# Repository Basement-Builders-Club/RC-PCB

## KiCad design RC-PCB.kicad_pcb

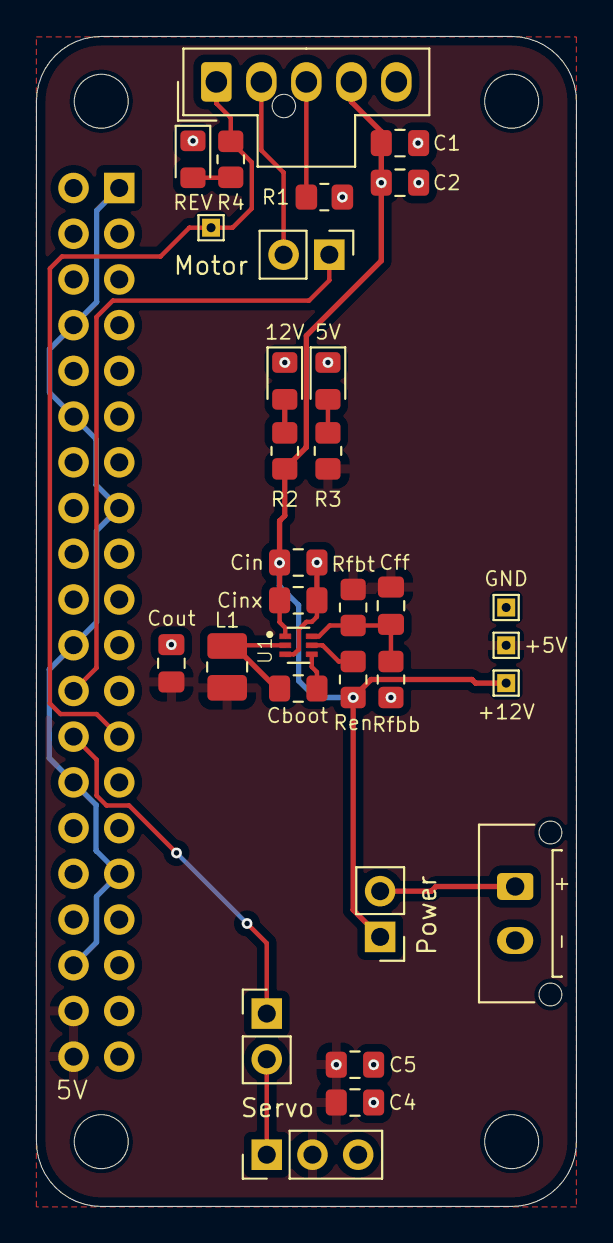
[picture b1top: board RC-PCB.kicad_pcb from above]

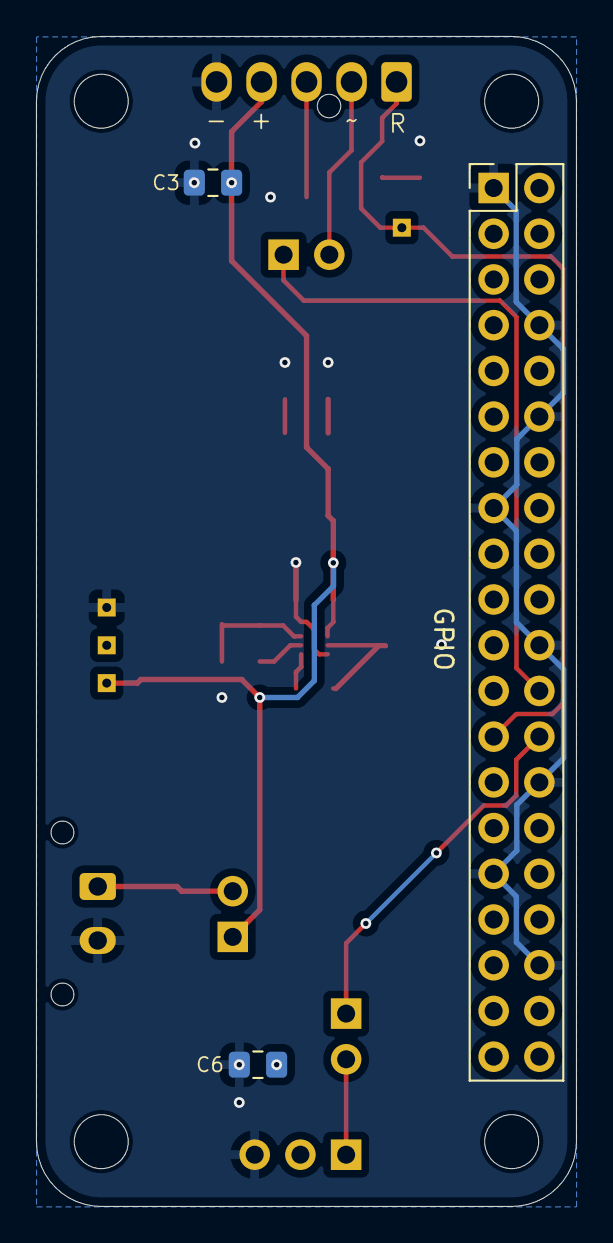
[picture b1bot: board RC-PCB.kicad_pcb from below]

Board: 2 copper layers, 30.0 x 65.0 mm, 38 parts (3 on the bottom side), 17 nets.

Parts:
5V, 12V: LED; LED_0805_2012Metric_Pad1.15x1.40mm_HandSolder
+5V, +12V: TP; TestPoint_THTPad_1.0x1.0mm_Drill0.5mm
Battery1: Conn_01x02; Molex_Micro-Fit_3.0_43650-0215_1x02_P3.00mm_Vertical
C1, C4: .1uF; C_0805_2012Metric_Pad1.18x1.45mm_HandSolder
C2, C3, C5, C6: 10uF; C_0805_2012Metric_Pad1.18x1.45mm_HandSolder
Cboot: 100nF; C_0805_2012Metric_Pad1.18x1.45mm_HandSolder
Cff: 47pF; C_0805_2012Metric_Pad1.18x1.45mm_HandSolder
Cin: 10uF; C_0805_2012Metric_Pad1.18x1.45mm_HandSolder
Cinx: 100nF; C_0805_2012Metric_Pad1.18x1.45mm_HandSolder
Cout: 22uF; C_0805_2012Metric_Pad1.18x1.45mm_HandSolder
GND: TP; TestPoint_THTPad_1.0x1.0mm_Drill0.5mm
GPIO: 40-Pin GPIO; PinHeader_2x20_P2.54mm_Vertical
H1, H2, H3, H4: MountingHole; MountingHole_3mm
L1: 3.3uH; L_1008_2520Metric_Pad1.43x2.20mm_HandSolder
Motor: Jumper_2_Open; PinHeader_1x02_P2.54mm_Vertical
Motor1: Conn_01x05; Molex_Nano-Fit_105309-xx05_1x05_P2.50mm_Vertical
Power: Jumper_2_Open; PinHeader_1x02_P2.54mm_Vertical
R1: 0; R_0805_2012Metric_Pad1.20x1.40mm_HandSolder
R2: 5.1k; R_0805_2012Metric_Pad1.20x1.40mm_HandSolder
R3: 1.5k; R_0805_2012Metric_Pad1.20x1.40mm_HandSolder
R4: 620; R_0805_2012Metric_Pad1.20x1.40mm_HandSolder
REV1: REV; LED_0805_2012Metric_Pad1.15x1.40mm_HandSolder
Ren: 100k; R_0805_2012Metric_Pad1.20x1.40mm_HandSolder
Rev2: TP; TestPoint_THTPad_1.0x1.0mm_Drill0.5mm
Rfbb: 30k; R_0805_2012Metric_Pad1.20x1.40mm_HandSolder
Rfbt: 220k; R_0805_2012Metric_Pad1.20x1.40mm_HandSolder
Servo: Jumper_2_Open; PinHeader_1x02_P2.54mm_Vertical
Servo1: Conn_01x03; PinHeader_1x03_P2.54mm_Vertical
U1: SOT50P160X60-6N

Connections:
+5V: +5V.1, C4.1, C5.1, C6.1, Cff.2, Cout.1, GPIO.38, GPIO.40, L1.1, R3.1, Rfbt.1, Servo1.2
+12V: +12V.1, C1.1, C2.1, C3.1, Cin.1, Cinx.1, Motor1.4, Power.1 (A), R2.1, Ren.2, U1.1 (VIN)
/Motor_PWM: GPIO.24, Motor.1 (A)
/Rev: GPIO.25, Motor1.1, R4.1, Rev2.1
/Servo_PWM: GPIO.26, Servo.1 (A)
GND: 5V.1 (K), 12V.1 (K), Battery1.2, C1.2, C2.2, C3.2, C4.2, C5.2, C6.2, Cin.2, Cinx.2, Cout.2, GND.1, GPIO.1, GPIO.8, GPIO.12, GPIO.15, GPIO.22, GPIO.28, GPIO.31, GPIO.36, Motor1.5, R1.2, REV1.1 (K), Rfbb.1, Servo1.3, U1.3 (GND)
unnamed: 5V.2 (A), R3.2
unnamed: 12V.2 (A), R2.2
unnamed: Battery1.1, Power.2 (B)
unnamed: Motor.2 (B), Motor1.2
unnamed: Motor1.3, R1.1
unnamed: R4.2, REV1.2 (A)
unnamed: Servo.2 (B), Servo1.1
unnamed: Cboot.2, U1.4 (BST)
unnamed: Ren.1, U1.5 (EN)
unnamed: Cff.1, Rfbb.2, Rfbt.2, U1.6 (FB)
unnamed: Cboot.1, L1.2, U1.2 (SW)

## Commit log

2025-03-29 First draft
2025-03-29 fixed fins, moved stuff around
2025-03-29 added 3D models
2025-04-06 finished routing
2025-04-06 ready to order
2025-04-11 ready to order pt 2
